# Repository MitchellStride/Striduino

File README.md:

# Striduino
 Easy 1602 lcd sized arduino carrier for quick prototypes.

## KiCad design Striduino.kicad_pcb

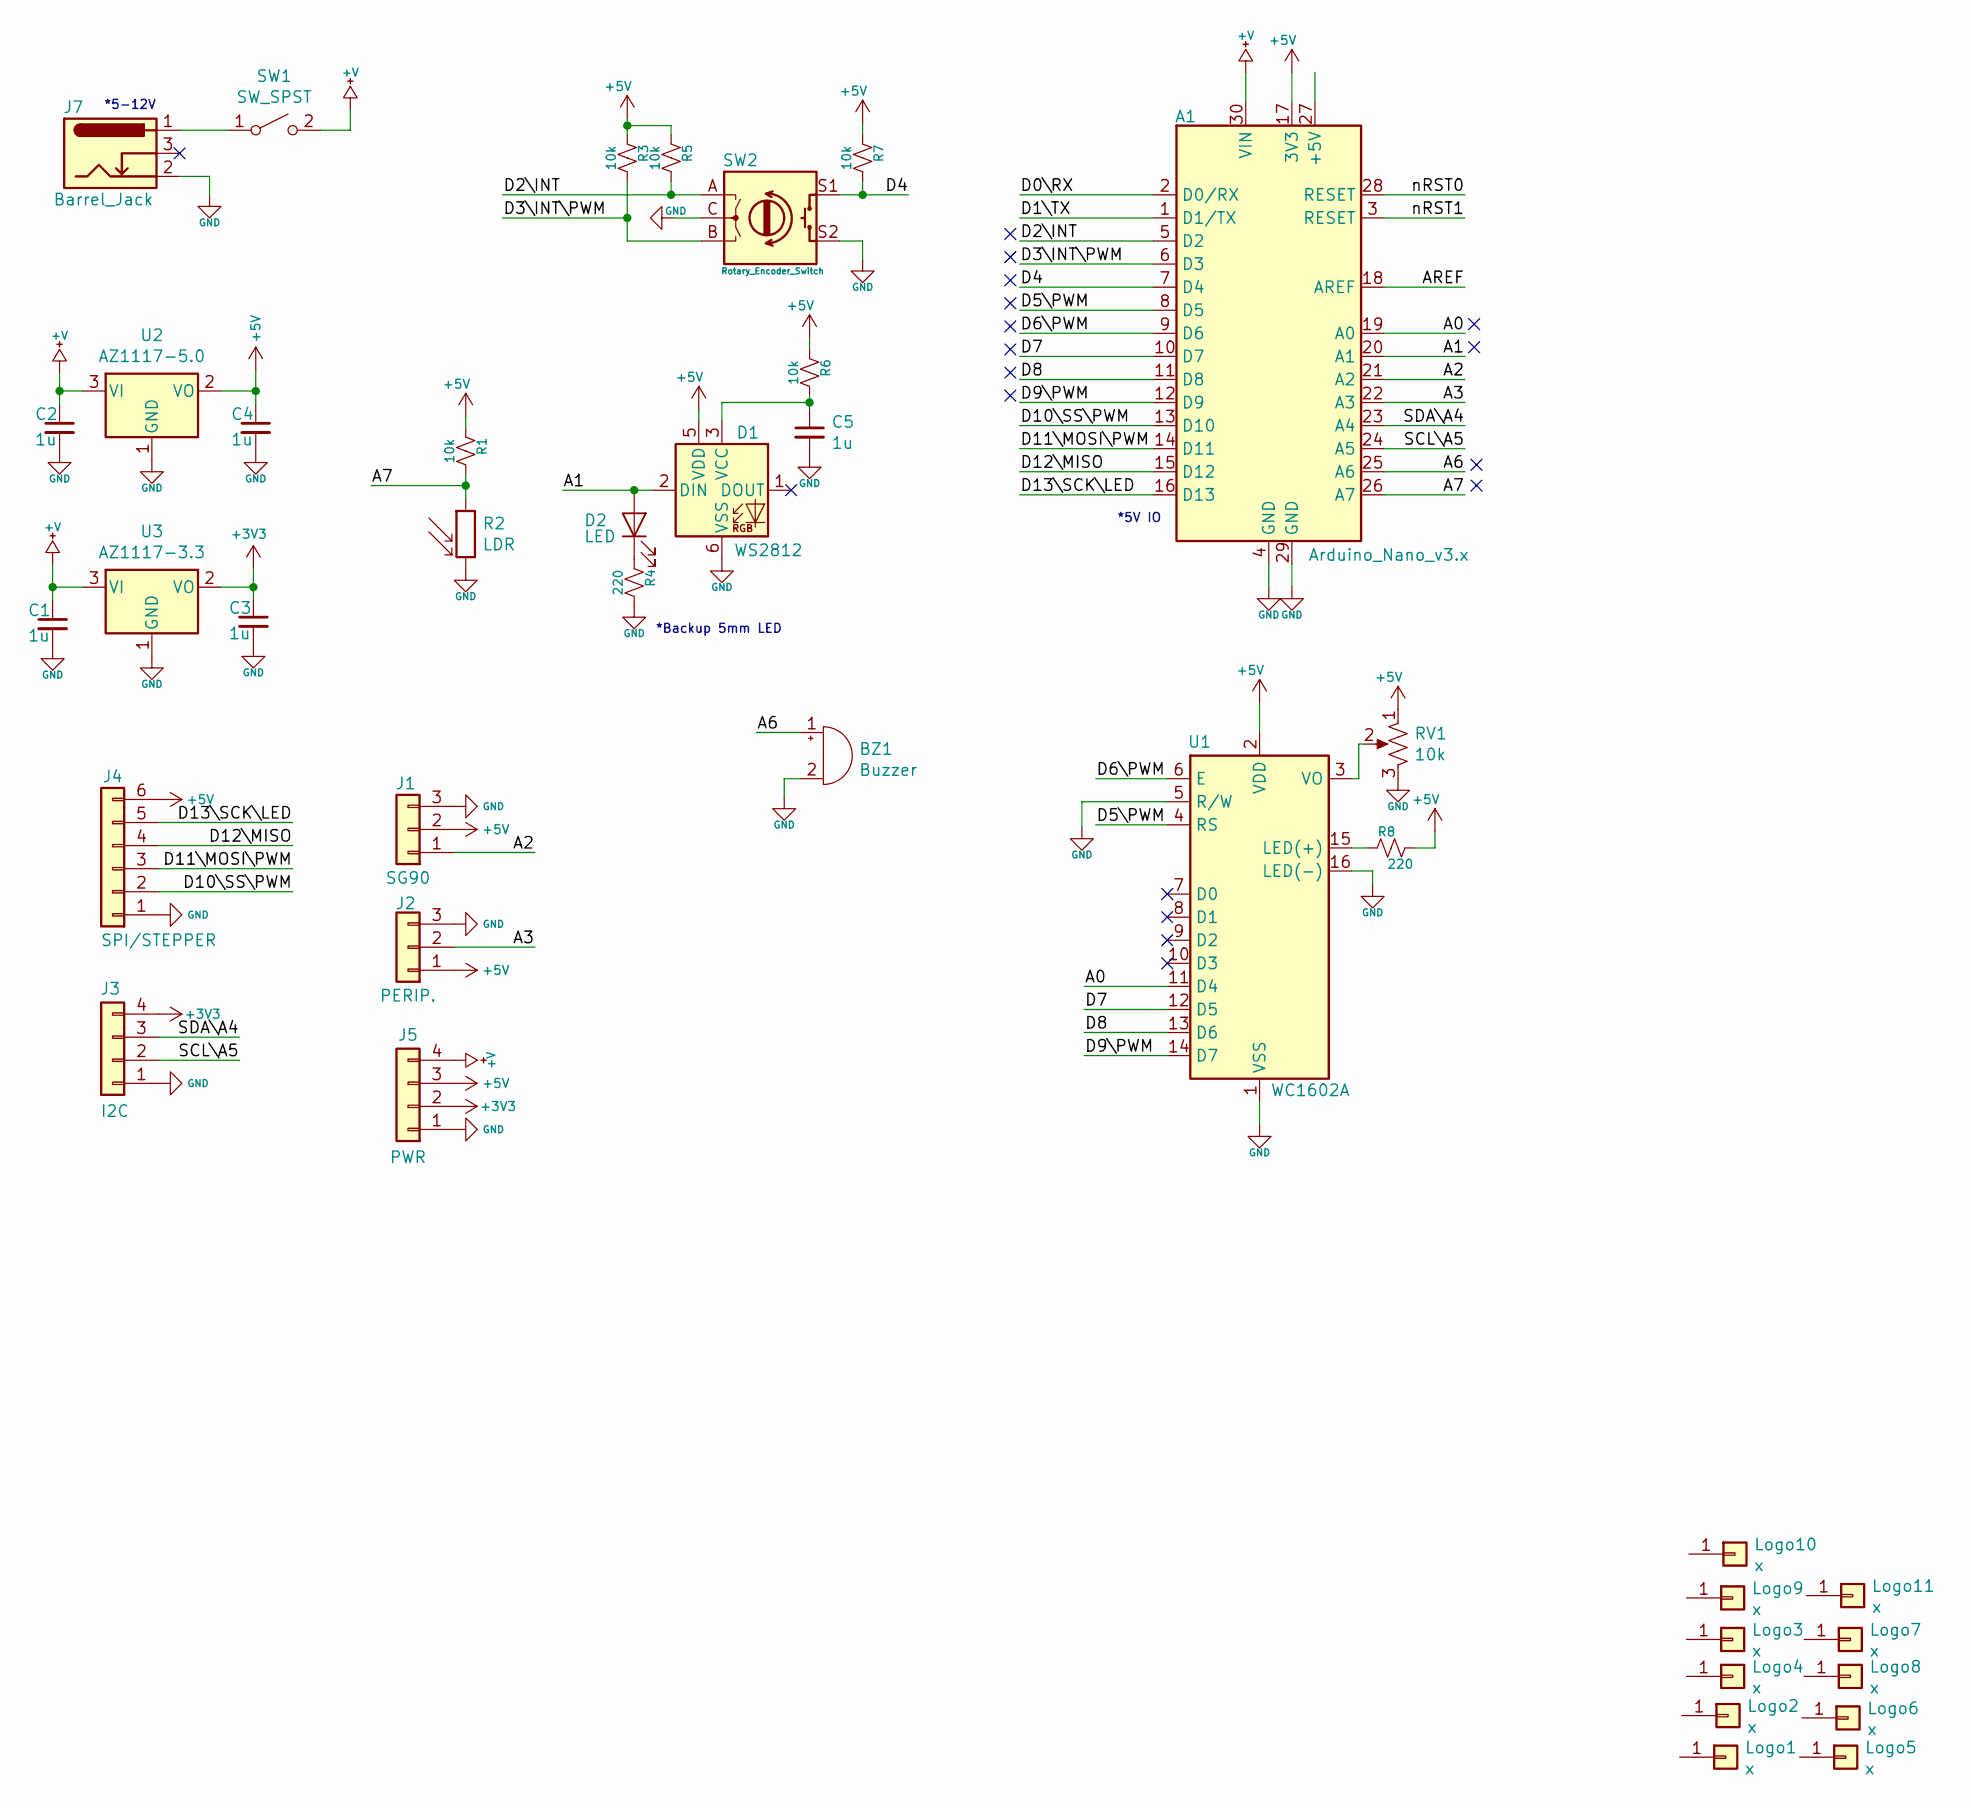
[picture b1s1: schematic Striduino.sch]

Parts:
A1: Arduino_Nano_v3.x; Arduino_Nano
BZ1: Buzzer; MagneticBuzzer_ProSignal_ABT-410-RC
C1, C2, C3, C4, C5: 1u; C_0603_1608Metric
D1: WS2812; LED_WS2812_PLCC6_5.0x5.0mm_P1.6mm
D2: LED; LED_D5.0mm
J1: SG90; PinHeader_1x03_P2.54mm_Horizontal
J2: PERIP.; PinHeader_1x03_P2.54mm_Horizontal
J3: I2C; PinHeader_1x04_P2.54mm_Horizontal
J4: SPI/STEPPER; PinHeader_1x06_P2.54mm_Horizontal
J5: PWR; PinHeader_1x04_P2.54mm_Horizontal
J7: Barrel_Jack; BarrelJack_Wuerth_6941xx301002
Logo1, Logo5: x; ESD-Logo_6.6x6mm_SilkScreen
Logo2: x; KiCad-Logo2_8mm_SilkScreen
Logo3, Logo7: x; datboi
Logo4: x; stride
Logo6, Logo8: x; SN_BLOCK
Logo9, Logo11: x; bolt
Logo10: x; chip
R1, R3, R5, R6, R7: 10k; R_0603_1608Metric
R2: LDR; R_Axial_DIN0207_L6.3mm_D2.5mm_P2.54mm_Vertical
R4, R8: 220; R_0603_1608Metric
RV1: 10k; Potentiometer_Bourns_TC33X_Vertical
SW1: SW_SPST; Switch_Toggle
SW2: Rotary_Encoder_Switch; RotaryEncoder_Alps_EC12E-Switch_Vertical_H20mm
U1: WC1602A
U2: AZ1117-5.0; SOT-223-3_TabPin2
U3: AZ1117-3.3; SOT-223-3_TabPin2

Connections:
+3V3: C3.1, J3.4, J5.2, U3.2 (VO)
+5V: A1.17 (3V3), C4.1, D1.5 (VDD), J1.2, J2.1, J4.6, J5.3, R1.2, R3.2, R5.2, R6.2, R7.2, R8.1, RV1.1, U1.2 (VDD), U2.2 (VO)
+V: A1.30 (VIN), C1.1, C2.1, J5.4, SW1.2 (B), U2.3 (VI), U3.3 (VI)
/A0: A1.19 (A0), U1.11 (D4)
/A1: A1.20 (A1), D1.2 (DIN), D2.2 (A)
/A2: A1.21 (A2), J1.1
/A3: A1.22 (A3), J2.2
/A6: A1.25 (A6), BZ1.1 (-)
/A7: A1.26 (A7), R1.1, R2.1
/AREF: A1.18 (AREF)
/D0\RX: A1.2 (D0/RX)
/D1\TX: A1.1 (D1/TX)
/D2\INT: A1.5 (D2), R5.1, SW2.A
/D3\INT\PWM: A1.6 (D3), R3.1, SW2.B
/D4: A1.7 (D4), R7.1, SW2.S1
/D5\PWM: A1.8 (D5), U1.4 (RS)
/D6\PWM: A1.9 (D6), U1.6 (E)
/D7: A1.10 (D7), U1.12 (D5)
/D8: A1.11 (D8), U1.13 (D6)
/D9\PWM: A1.12 (D9), U1.14 (D7)
/D10\SS\PWM: A1.13 (D10), J4.2
/D11\MOSI\PWM: A1.14 (D11), J4.3
/D12\MISO: A1.15 (D12), J4.4
/D13\SCK\LED: A1.16 (D13), J4.5
/SCL\A5: A1.24 (A5), J3.2
/SDA\A4: A1.23 (A4), J3.3
/nRST0: A1.28 (RESET)
/nRST1: A1.3 (RESET)
GND: A1.4 (GND), A1.29 (GND), BZ1.2 (+), C1.2, C2.2, C3.2, C4.2, C5.2, D1.6 (VSS), J1.3, J2.3, J3.1, J4.1, J5.1, J7.2, R2.2, R4.1, RV1.3, SW2.C, SW2.S2, U1.1 (VSS), U1.5 (R/W), U1.16 (LED(-)), U2.1 (GND), U3.1 (GND)
unnamed: C5.1, D1.3 (VCC), R6.1
unnamed: D2.1 (K), R4.2
unnamed: J7.1, SW1.1 (A)
unnamed: R8.2, U1.15 (LED(+))
unnamed: RV1.2, U1.3 (VO)

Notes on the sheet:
*Backup 5mm LED
*5-12V
*5V IO

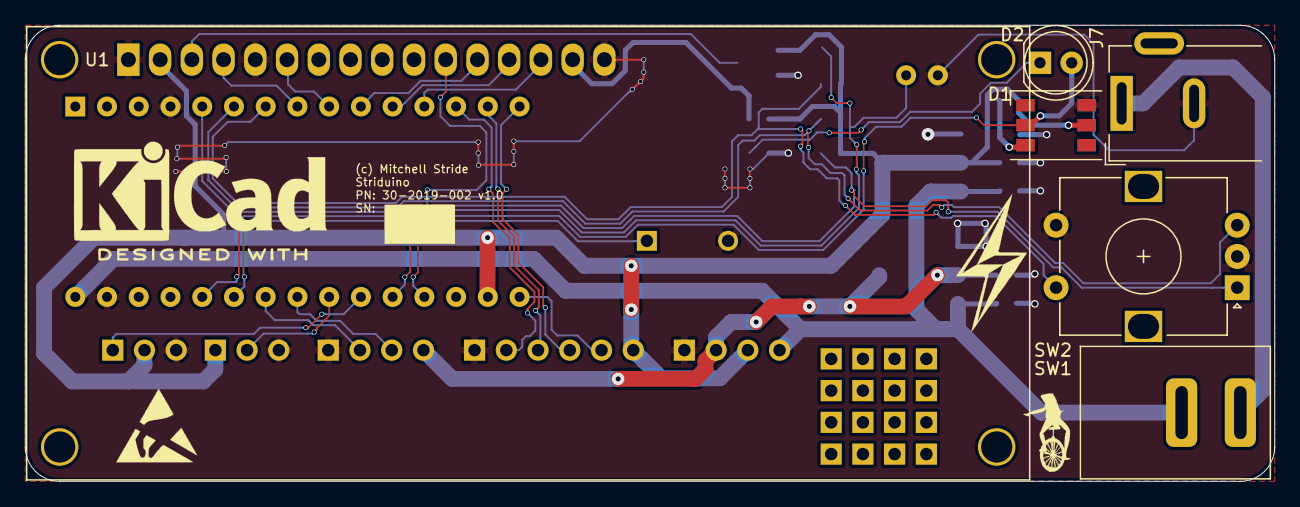
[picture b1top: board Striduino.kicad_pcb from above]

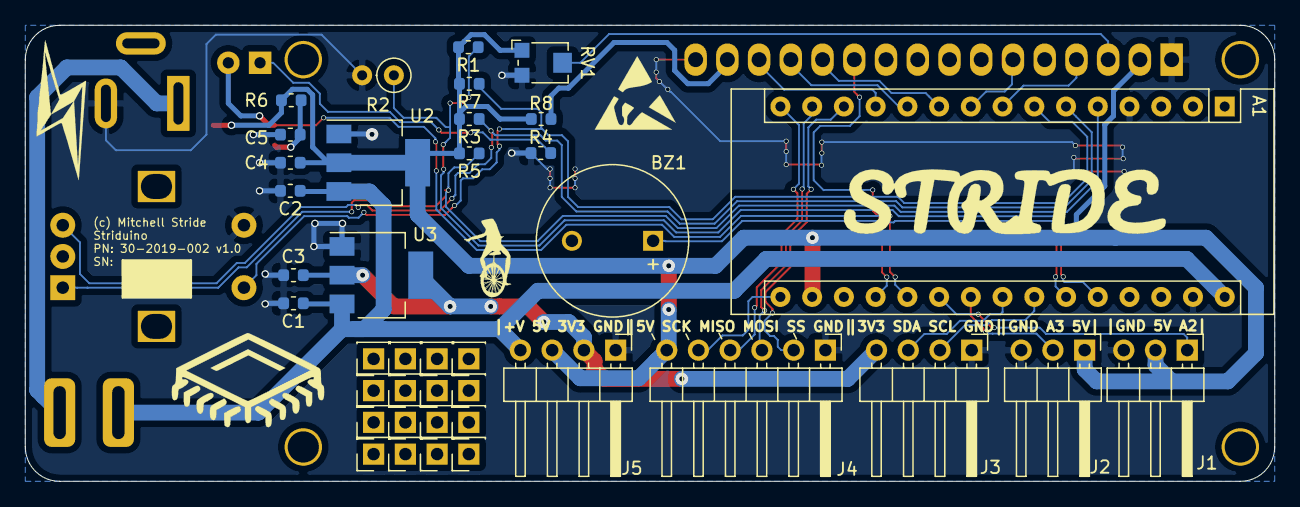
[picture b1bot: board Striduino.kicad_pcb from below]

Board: 2 copper layers, 100.0 x 36.5 mm, 40 parts (29 on the bottom side), 29 nets.

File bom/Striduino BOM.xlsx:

BOM
Item # | Quantitiy | Value | References | Package | Description | Manufacturer | Manufacturer PN | Supplier | Supplier PN | Unit Cost [$CAD] | Extended [$CAD] | Notes: | Alternates
1.0 | 1.0 | WS2812 | D1 | LED_WS2812_PLCC6_5.0x5.0mm_P1.6mm |  |  |  |  | 1568-1800-ND |  |  |  |  |  |  |  | WS2812
2.0 | 5.0 | 1u | C1,C2,C3,C4,C5 | C_0603_1608Metric |  |  |  |  | 1276-1019-1-ND |  |  |  |  |  |  |  | 1u
3.0 | 1.0 | SG90 PERIP. SPI/STEPPER I2C PWR | J1-5 | PinHeader_1x03_P2.54mm_Horizontal |  |  |  |  | S1111EC-23-ND |  |  |  |  |  |  |  | PERIP.
4.0 | 5.0 | 10k | R1,R3,R5,R6,R7 | R_0603_1608Metric |  |  |  |  | RNCP0603FTD10K0CT-ND |  |  |  |  |  |  |  | 10k
5.0 | 2.0 | 220.0 | R4,R8 | R_0603_1608Metric |  |  |  |  | A129680CT-ND |  |  |  |  |  |  |  | 220.0
6.0 | 1.0 | AZ1117-5.0 | U2 | SOT-223-3_TabPin2 |  |  |  |  | AZ1117EH-5.0TRG1DICT-ND |  |  |  |  |  |  |  | AZ1117-5.0
7.0 | 1.0 | AZ1117-3.3 | U3 | SOT-223-3_TabPin2 |  |  |  |  | AZ1117EH-3.3TRG1DICT-ND |  |  |  |  |  |  |  | AZ1117-3.3
8.0 | 1.0 | 10k | RV1 | Potentiometer_Bourns_TC33X_Vertical |  |  |  |  | TC33X-1-103ECT-ND |  |  |  |  |  |  |  | 10k
9.0 | 1.0 |  | SW2 | RotaryEncoder_Alps_EC12E-Switch_Vertical_H20mm |  |  |  |  | X
 | ALIEXPRESS
10.0 | 1.0 | Arduino_Nano_v3.x | A1 | Arduino_Nano |  |  |  |  | Order 2 |  |  |  |  |  |  |  | Arduino_Nano_v3.x
11.0 | 1.0 | Barrel_Jack | J7 | BarrelJack_Wuerth_6941xx301002 |  |  |  |  | X |  |  |  |  |  |  |  | Barrel_Jack
12.0 | 1.0 | SW_SPST | SW1 | Switch_Toggle |  |  |  |  | X |  |  |  |  |  |  |  | SW_SPST
13.0 | 1.0 | LED | D2 | LED_D5.0mm |  |  |  |  | X |  |  |  |  |  |  |  | LED
14.0 | 1.0 | SG90 | J1 | PinHeader_1x03_P2.54mm_Horizontal |  |  |  |  | Order 1 |  |  |  |  |  |  |  | SG90
15.0 | 1.0 | Buzzer | BZ1 | MagneticBuzzer_ProSignal_ABT-410-RC |  |  |  |  | X |  |  |  |  |  |  |  | Buzzer
16.0 | 1.0 | WC1602A | U1 | WC1602A |  |  |  |  | X |  |  |  |  |  |  |  | WC1602A
17.0 | 1.0 | LDR | R2 | R_Axial_DIN0207_L6.3mm_D2.5mm_P2.54mm_Vertical |  |  |  |  | Order pck |  |  |  |  |  |  |  | LDR

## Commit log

2019-11-25 added almost complete pcb
2019-11-25 Ordered PCB V1.0
    Order boards to home for dec. ordered ali to ON for jan. wait till then to test around.
2019-11-25 added pics
2019-11-26 cropped pics
2021-11-03 2021 changes upload
